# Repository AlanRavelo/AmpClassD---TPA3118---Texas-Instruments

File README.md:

# Amplificador clase D / Op-amp Single Power
============================================
# KICAD 7.0

# TPA3118D2

El TPA3118D2 es un circuito integrado de Texas Instruments que se utiliza como amplificador de audio de clase D. Este amplificador utiliza una técnica de modulación de ancho de pulso (PWM) para lograr una alta eficiencia en la amplificación de la señal de audio.

Cuenta con dos canales de amplificación de audio que pueden manejar una carga de altavoz de hasta 30W por canal, con una eficiencia de hasta el 90%. Además, el circuito integrado tiene una amplia gama de voltaje de entrada, lo que lo hace adecuado para diversas aplicaciones de audio.

Posee una serie de características de protección, como protección contra cortocircuitos y sobrecalentamiento, lo que lo hace seguro y confiable en su operación. También cuenta con una función de ganancia seleccionable, lo que permite ajustar la ganancia de amplificación de acuerdo a la aplicación.

Su uso es muy popular en aplicaciones de audio de alta calidad, como sistemas de cine en casa, sistemas de audio de alta fidelidad y sistemas de sonido de automóviles, debido a su alta eficiencia, calidad de sonido y facilidad de uso.

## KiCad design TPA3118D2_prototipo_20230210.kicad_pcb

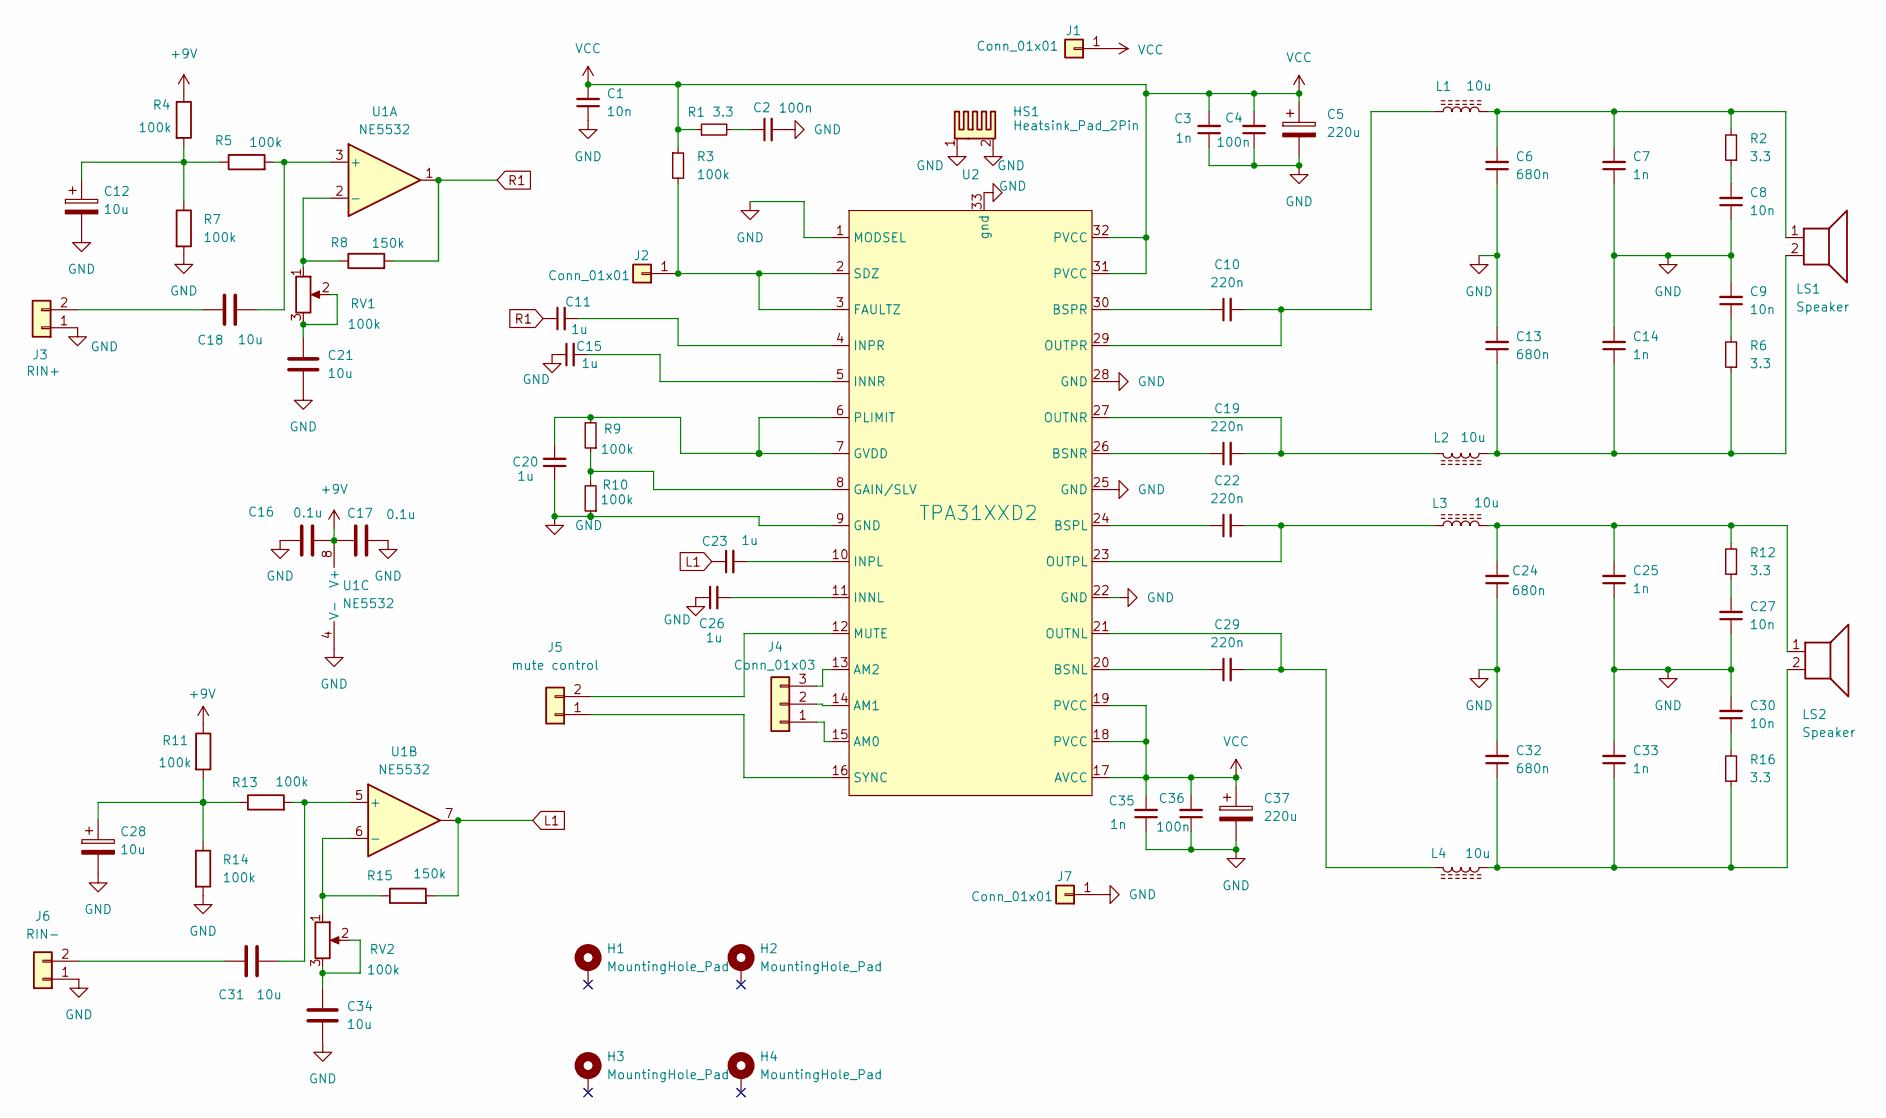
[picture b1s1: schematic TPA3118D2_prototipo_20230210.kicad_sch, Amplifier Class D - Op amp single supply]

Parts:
C1, C8, C9, C27, C30: 10n; C_Disc_D3.0mm_W1.6mm_P2.50mm
C2, C4, C36: 100n; C_Disc_D3.0mm_W1.6mm_P2.50mm
C3, C7, C14, C25, C33, C35: 1n; C_Disc_D3.0mm_W1.6mm_P2.50mm
C5, C37: 220u; C_Disc_D3.0mm_W1.6mm_P2.50mm
C6, C13, C24, C32: 680n; C_Rect_L7.0mm_W3.5mm_P5.00mm
C10, C19, C22, C29: 220n; C_Disc_D3.0mm_W1.6mm_P2.50mm
C11, C15, C20, C23, C26: 1u; C_Disc_D3.0mm_W1.6mm_P2.50mm
C12, C18, C21, C28, C31, C34: 10u; C_Disc_D3.0mm_W1.6mm_P2.50mm
C16, C17: 0.1u; C_Disc_D3.0mm_W1.6mm_P2.50mm
H1, H2, H3, H4: MountingHole_Pad; MountingHole_3.7mm_Pad
HS1: Heatsink_Pad_2Pin; Disipador
J1, J2, J7: Conn_01x01; Pin_D0.7mm_L6.5mm_W1.8mm_FlatFork
J3: RIN+; RCA_RCJ-04
J4: Conn_01x03; PinSocket_1x03_P2.54mm_Vertical
J5: mute control; PinSocket_1x02_P2.54mm_Vertical
J6: RIN-; RCA_RCJ-04
L1, L2, L3, L4: 10u; L_12x12mm_H8mm
LS1, LS2: Speaker; TerminalBlock_Phoenix_MKDS-1,5-2_1x02_P5.00mm_Horizontal
R1, R2, R6, R12, R16: 3.3; R_Axial_DIN0204_L3.6mm_D1.6mm_P5.08mm_Horizontal
R3, R4, R5, R7, R9, R10, R11, R13, R14: 100k; R_Axial_DIN0204_L3.6mm_D1.6mm_P5.08mm_Horizontal
R8, R15: 150k; R_Axial_DIN0204_L3.6mm_D1.6mm_P5.08mm_Horizontal
RV1, RV2: 100k; Potentiometer_Bourns_3266W_Vertical
U1: NE5532; SOIC-8_3.9x4.9mm_P1.27mm
U2: TPA31XXD2; TPA3118D2DAPR

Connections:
+9V: C16.2, C17.1, R4.1, R11.1, U1.8 (V+)
GND: C1.1, C2.2, C3.1, C4.1, C5.2, C6.1, C7.1, C8.1, C9.2, C12.2, C13.2, C14.2, C15.1, C16.1, C17.2, C20.1, C21.1, C24.1, C25.1, C26.1, C27.1, C28.2, C30.2, C32.2, C33.2, C35.1, C36.1, C37.2, HS1.1, HS1.2, J3.1, J6.1, J7.1, R7.2, R10.1, R14.2, U1.4 (V-), U2.1 (MODSEL), U2.9 (GND), U2.22 (GND), U2.25 (GND), U2.28 (GND), U2.33 (gnd)
L1: C23.1, R15.2, U1.7
unnamed: C2.1, R1.2
unnamed: C6.2, C7.2, L1.2, LS1.1, R2.2
unnamed: C8.2, R2.1
unnamed: C9.1, R6.2
unnamed: C10.1, U2.30 (BSPR)
unnamed: C10.2, L1.1, U2.29 (OUTPR)
unnamed: C11.2, U2.4 (INPR)
unnamed: C12.1, R4.2, R5.1, R7.1
unnamed: C13.1, C14.1, L2.1, LS1.2, R6.1
unnamed: C15.2, U2.5 (INNR)
unnamed: C18.2, R5.2, U1.3 (+)
unnamed: C19.1, U2.26 (BSNR)
unnamed: C19.2, L2.2, U2.27 (OUTNR)
unnamed: C20.2, R9.2, U2.6 (PLIMIT), U2.7 (GVDD)
unnamed: C22.1, U2.24 (BSPL)
unnamed: C22.2, L3.1, U2.23 (OUTPL)
unnamed: C23.2, U2.10 (INPL)
unnamed: C24.2, C25.2, L3.2, LS2.1, R12.2
unnamed: C26.2, U2.11 (INNL)
unnamed: C27.2, R12.1
unnamed: C28.1, R11.2, R13.1, R14.1
unnamed: C29.1, U2.20 (BSNL)
unnamed: C29.2, L4.2, U2.21 (OUTNL)
unnamed: C30.1, R16.2
unnamed: C31.1, J6.2
unnamed: C31.2, R13.2, U1.5 (+)
unnamed: C32.1, C33.1, L4.1, LS2.2, R16.1
unnamed: C34.2, RV2.2, RV2.3
unnamed: J2.1, R3.2, U2.2 (SDZ), U2.3 (FAULTZ)
unnamed: C18.1, J3.2
unnamed: J4.1, U2.15 (AM0)
unnamed: J4.2, U2.14 (AM1)
unnamed: J4.3, U2.13 (AM2)
unnamed: J5.1, U2.16 (SYNC)
unnamed: J5.2, U2.12 (MUTE)
unnamed: R8.1, RV1.1, U1.2 (-)
unnamed: R9.1, R10.2, U2.8 (GAIN/SLV)
unnamed: R15.1, RV2.1, U1.6 (-)
unnamed: C21.2, RV1.2, RV1.3
R1: C11.1, R8.2, U1.1
VCC: C1.2, C3.2, C4.2, C5.1, C35.2, C36.2, C37.1, J1.1, R1.1, R3.1, U2.17 (AVCC), U2.18 (PVCC), U2.19 (PVCC), U2.31 (PVCC), U2.32 (PVCC)

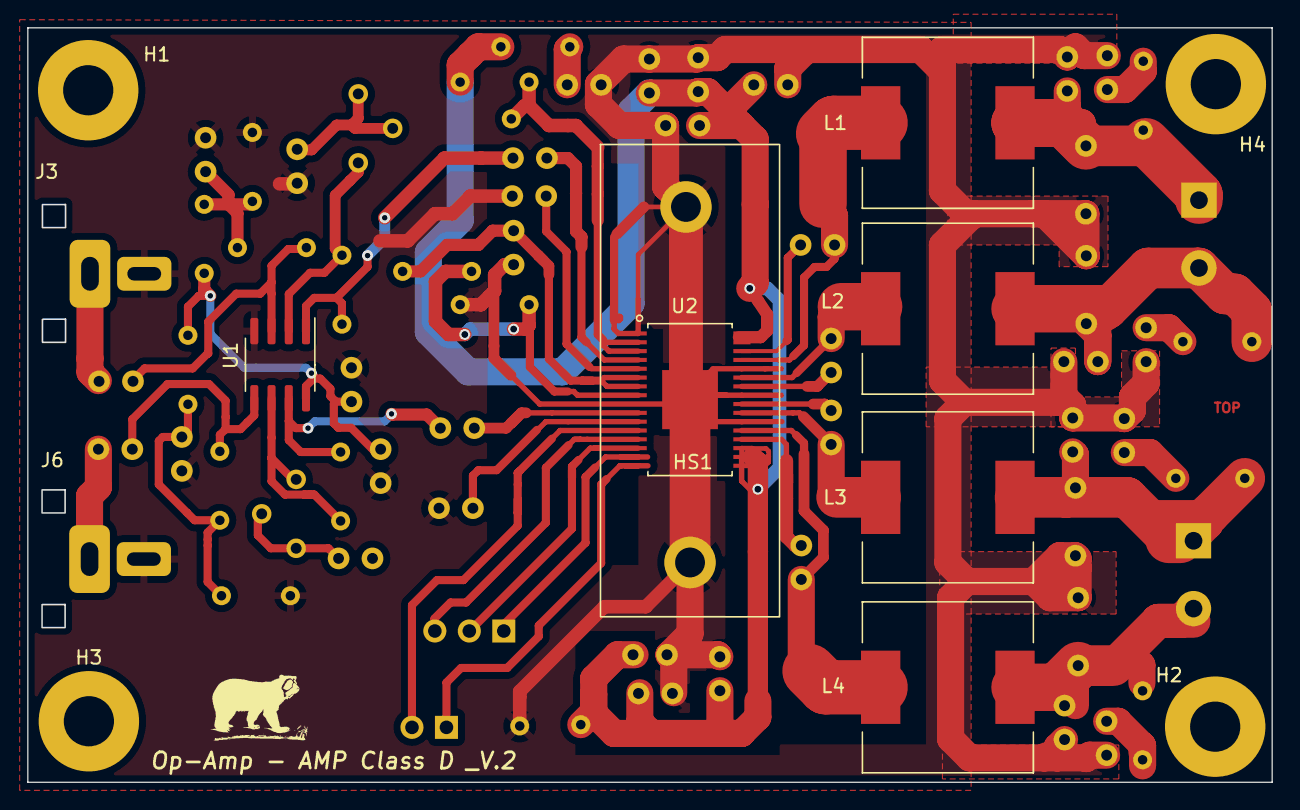
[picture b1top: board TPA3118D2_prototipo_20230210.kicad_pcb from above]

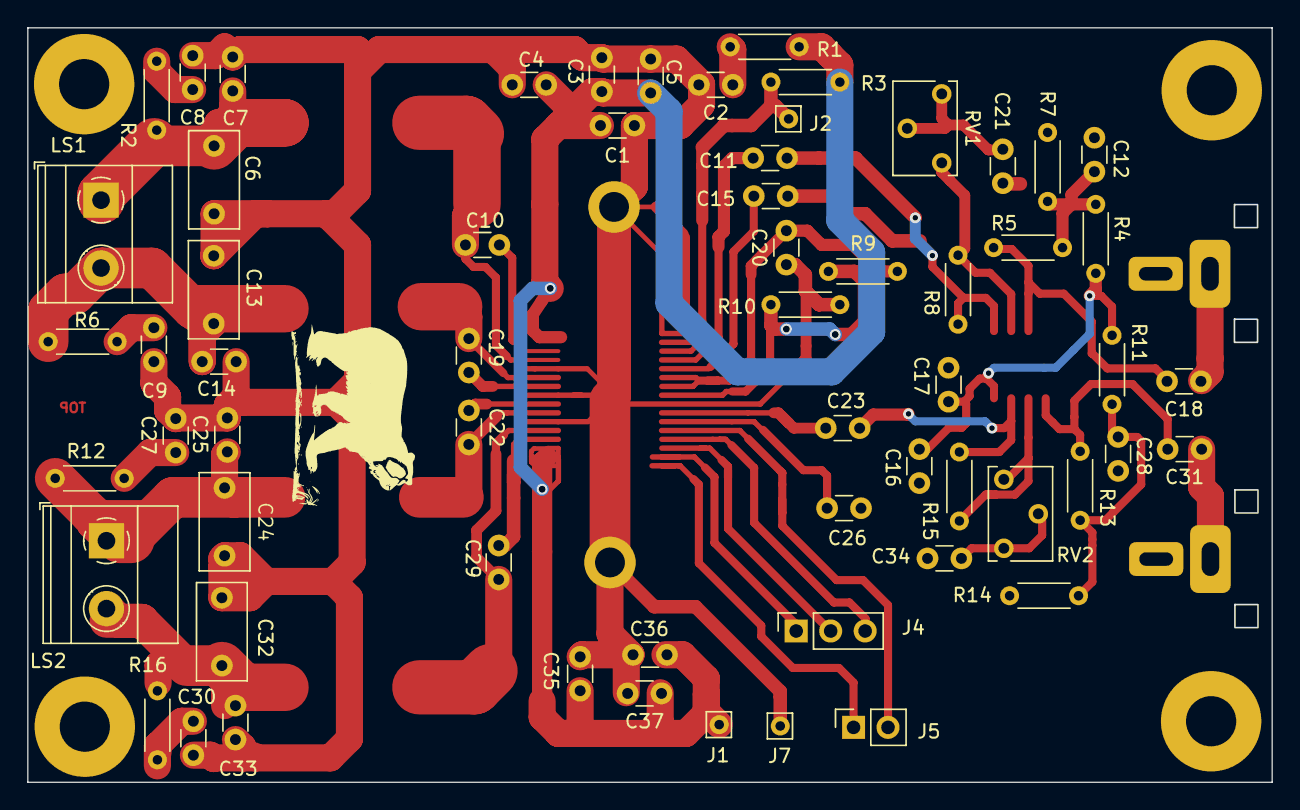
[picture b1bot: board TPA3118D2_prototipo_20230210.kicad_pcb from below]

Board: 2 copper layers, 91.7 x 55.6 mm, 76 parts (62 on the bottom side), 44 nets.

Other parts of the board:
G: LOGO; oso_logo02

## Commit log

2023-02-22 Create Gerber

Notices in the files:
parts and their libraries:
Copyright 2021 Accelerated Designs. All rights reserved.
